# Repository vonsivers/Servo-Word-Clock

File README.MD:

# Servo Wordclock - Version 2

Wordclock controlled by 114 servos. Improved version 2

## BoM
see "BoM.xls"

## Detailed Build Instructions
see "Assembly Instructions.pdf"

## Laser Cut
see files in folder dxf

quantity, materials and thicknesses specified in BoM

## 3D Printing
see files in folder stl

quantity and recommended materials specified in BoM

stl files named "Any" have slightly looser tolerances

## PCBs
see folder PCBs

LED_board was ordered as PCBA from PCBWay.com with black solder mask

wordclock_mainPCB was ordered as bare PCB from aisler.net

## Links
[demo video on YouTube](https://youtu.be/Euf8V2k0oOI)

[Hackaday.io project link](https://hackaday.io/project/166546-servo-controlled-word-clock-v2)

[Instructables project link](https://www.instructables.com/Servo-Wordclock-V2/)

[Version 1 Instructables project link](https://www.instructables.com/Word-Clock-Controlled-by-114-Servos/)

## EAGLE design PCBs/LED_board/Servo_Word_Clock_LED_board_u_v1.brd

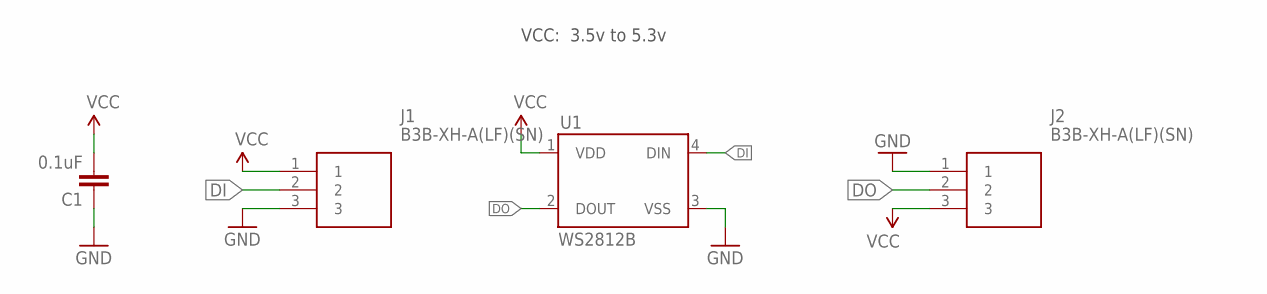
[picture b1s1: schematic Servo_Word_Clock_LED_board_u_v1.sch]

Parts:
C1: 0.1uF; 0603-CAP
J1, J2: B3B-XH-A(LF)(SN); SHDR3W64P0X250_1X3_990X575X700
U1: WS2812B

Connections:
DI: J1.2, U1.4 (DIN)
DO: J2.2, U1.2 (DOUT)
GND: C1.1, J1.3, J2.1, U1.3 (VSS)
VCC: C1.2, J1.1, J2.3, U1.1 (VDD)

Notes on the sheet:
VCC: 3.5v to 5.3v

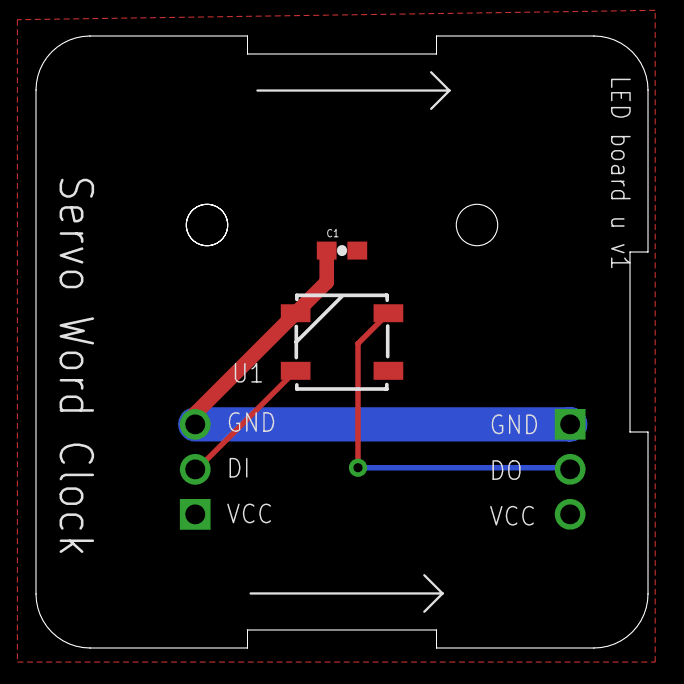
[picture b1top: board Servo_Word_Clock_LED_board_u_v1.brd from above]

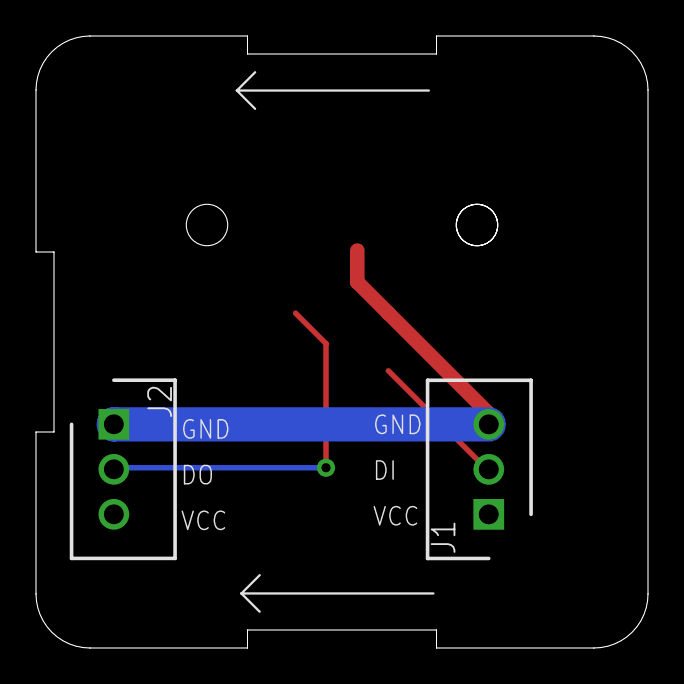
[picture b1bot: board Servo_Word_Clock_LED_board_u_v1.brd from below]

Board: 2 copper layers, 34.0 x 34.0 mm, 4 parts (2 on the bottom side), 4 nets.

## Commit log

2019-08-20 PCB files added
2019-09-08 added lincense file
2019-10-27 first version
2019-10-29 first really working version
2019-11-02 bug fixes
2019-11-20 Night Mode page added
    added page for night mode, added blinking clock symbol
2019-11-21 night mode added
    added night mode for swirching clock of or silent
2019-11-21 bug fixes
    night mode start time can now be larger than end time
2019-11-25 added advanced config
    added hidden advanced config options, random color bug fix, deleted other files, added lincense statement
2019-11-27 new transition between clock modes
    initialize servo position according to current clockmode; servos move slowly when changing clock mode to silent or off
2019-12-01 removed servo sleep, reassigned pins
    servo sleep mode removed, LED pin newly assigned, "no NTP" animation fixed
2020-02-27 adjusted minimum brightness to 50
2020-05-04 Added ESP8266 compatibility
    Code made compatible with ESP8266
    Fixed Exception(3) bug
    Added asynchronous WiFi search
2020-05-11 OTA + password protection
    added OTA update
    added password protection for webserver
2020-05-15 no NTP animation removed
    removed fade-in/out of clock symbol since it glitches on ESP8266
    corrected PCA9685 address
2020-11-18 added new GUI
2021-01-28 updated dependancies
2021-01-28 api update, login integriert
2021-01-28 added login and wifi settings
2021-01-29 added change password tab
2021-01-29 change pw & keep alive integriert
2021-01-29 changed path names
2021-01-29 edited Readme
2021-01-29 added move-move-build.js
2021-01-31 added build script
2021-02-01 changed ESP Filesystem, bugfixing
2021-02-01 added readme
2021-02-01 resized pics
2021-04-10 changed folder structure
2021-04-13 added MCU functions
2021-04-17 debugging
2021-04-18 debugged time change
2021-04-18 bug fixing in GUI
2021-04-19 added city names as timezones
2021-04-19 removed DST from timesettings
2021-04-19 added date to custom time
2021-04-19 changed timezone to select box
2021-08-22 mDNS fix
    fixed mDNS
    fixed minimum brightness
    set default color and effects to random
2021-10-10 added manual and buglist, updated clearFirmware.ino
2021-11-04 sleepmode for servos
2021-11-28 updated for Adafruit Servo Library 2.4.0
2021-12-12 servomax position increased to 800
2022-03-24 added stl, dxf files
    added asssembly instructions, BoM, dxf, stl files
2022-03-25 updated BoM and assembly instructions
2022-03-27 updated Assembly instructions
2022-05-02 added stl files
2022-05-04 added different gear diameters
2025-06-24 Bump pbkdf2 from 3.1.1 to 3.1.3 in /code/servowordclock-gui-develop
    Bumps [pbkdf2](https://github.com/crypto-browserify/pbkdf2) from 3.1.1 to 3.1.3.
    - [Changelog](https://github.com/browserify/pbkdf2/blob/master/CHANGELOG.md)
    - [Commits](https://github.com/crypto-browserify/pbkdf2/compare/v3.1.1...v3.1.3)
    ---
    updated-dependencies:
    - dependency-name: pbkdf2
2025-07-17 Bump on-headers and compression in /code/servowordclock-gui-develop
    Bumps [on-headers](https://github.com/jshttp/on-headers) and [compression](https://github.com/expressjs/compression). These dependencies needed to be updated together.
    Updates `on-headers` from 1.0.2 to 1.1.0
    - [Release notes](https://github.com/jshttp/on-headers/releases)
    - [Changelog](https://github.com/jshttp/on-headers/blob/master/HISTORY.md)
    - [Commits](https://github.com/jshttp/on-headers/compare/v1.0.2...v1.1.0)
    Updates `compression` from 1.7.4 to 1.8.1
2025-08-21 Bump sha.js from 2.4.11 to 2.4.12 in /code/servowordclock-gui-develop
    Bumps [sha.js](https://github.com/crypto-browserify/sha.js) from 2.4.11 to 2.4.12.
    - [Changelog](https://github.com/browserify/sha.js/blob/master/CHANGELOG.md)
    - [Commits](https://github.com/crypto-browserify/sha.js/compare/v2.4.11...v2.4.12)
    ---
    updated-dependencies:
    - dependency-name: sha.js
2025-08-21 Bump cipher-base from 1.0.4 to 1.0.6 in /code/servowordclock-gui-develop
    Bumps [cipher-base](https://github.com/crypto-browserify/cipher-base) from 1.0.4 to 1.0.6.
    - [Changelog](https://github.com/browserify/cipher-base/blob/master/CHANGELOG.md)
    - [Commits](https://github.com/crypto-browserify/cipher-base/compare/v1.0.4...v1.0.6)
    ---
    updated-dependencies:
    - dependency-name: cipher-base
2025-11-18 Bump js-yaml from 3.13.1 to 3.14.2 in /code/servowordclock-gui-develop
    Bumps [js-yaml](https://github.com/nodeca/js-yaml) from 3.13.1 to 3.14.2.
    - [Changelog](https://github.com/nodeca/js-yaml/blob/master/CHANGELOG.md)
    - [Commits](https://github.com/nodeca/js-yaml/compare/3.13.1...3.14.2)
    ---
    updated-dependencies:
    - dependency-name: js-yaml
2025-11-27 Bump node-forge and preact-cli in /code/servowordclock-gui-develop
    Bumps [node-forge](https://github.com/digitalbazaar/forge) to 1.3.2 and updates ancestor dependency [preact-cli](https://github.com/preactjs/preact-cli/tree/HEAD/packages/cli). These dependencies nee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
    Updates `node-forge` from 0.10.0 to 1.3.2
    - [Changelog](https://github.com/digitalbazaar/forge/blob/main/CHANGELOG.md)
    - [Commits](https://github.com/digitalbazaar/forge/compare/0.10.0...v1.3.2)
    Updates `preact-cli` from 3.0.5 to 3.5.1
    - [Release notes](https://github.com/preactjs/preact-cli/releases)
2026-01-24 Bump lodash from 4.17.20 to 4.17.23 in /code/servowordclock-gui-develop
    Bumps [lodash](https://github.com/lodash/lodash) from 4.17.20 to 4.17.23.
    - [Release notes](https://github.com/lodash/lodash/releases)
    - [Commits](https://github.com/lodash/lodash/compare/4.17.20...4.17.23)
    ---
    updated-dependencies:
    - dependency-name: lodash
2026-02-03 Bump url-parse from 1.4.7 to 1.5.10 in /code/servowordclock-gui-develop
    Bumps [url-parse](https://github.com/unshiftio/url-parse) from 1.4.7 to 1.5.10.
    - [Commits](https://github.com/unshiftio/url-parse/compare/1.4.7...1.5.10)
    ---
    updated-dependencies:
    - dependency-name: url-parse
    dependency-version: 1.5.10

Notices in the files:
parts and their libraries:
SparkFun-Capacitors: Licensing: Creative Commons ShareAlike 4.0 International - https://creativecommons.org/licenses/by-sa/4.0
SparkFun-LED: Licensing: CC v3.0 Share-Alike You are welcome to use this library for commercial purposes.
